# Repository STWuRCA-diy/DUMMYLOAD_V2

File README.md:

IMPORTANT!

Unfortunately, I did not have enough time to verify whether the shared version of the board contains any errors. This is a hobby project and I also had to focus on my day job.

I hope someone from the community will be able to review the design, confirm that everything is correct, or fix any mistakes I may have left behind.

The first version of the board did not include many of the components that are present in the shared version. However, all of them were tested using bodge wiring and then added to the shared design.

Good luck!

DUMMYLOAD_V2

High-Voltage Electronic Dummy Load (Non-Commercial, Open-Source)

DUMMYLOAD_V2 is an open-source, non-commercial electronic dummy load designed for testing high-voltage linear power supplies, especially those used in tube (valve) amplifier circuits.

The project includes hardware (PCB), firmware, and mechanical enclosure, forming a complete DIY measurement and load solution for HV power supply development and testing.

Key Features
	•	Adjustable constant-current load
	•	High-voltage measurement via resistor divider
	•	Current measurement using INA219
	•	Protection logic implemented in firmware
	•	Stand-alone operation (no PC required)

Electrical Characteristics
	•	Load mode: Constant Current (CC)
	•	Current regulation range: 0 – ~400 mA (firmware-controlled, step-based)
	•	Voltage measurement

⚠️ HIGH VOLTAGE WARNING

This project is intended for experienced users.

High voltages used in tube power supplies can be lethal.

	•	Use proper insulation and creepage distances
	•	Never touch the circuit during operation
	•	The author assumes no responsibility for misuse

If you are not comfortable working with HV — do not build or use this device.

⸻

📜 License (Very Important)

🔒 Non-Commercial Only

This entire project is licensed under:

Creative Commons Attribution-NonCommercial 4.0 International
(CC BY-NC 4.0)

🍺 Friendly Note

If you ever meet me in person and find this project useful,
you owe me a beer.

If we happen to be in a country where it is legal,
a joint is also acceptable 🙂

This is a friendly gesture — not a legal obligation.

⸻

❤️ Credits

Designed and shared by STWuRCA-diy
DIY spirit, tube amps & open hardware 🤘

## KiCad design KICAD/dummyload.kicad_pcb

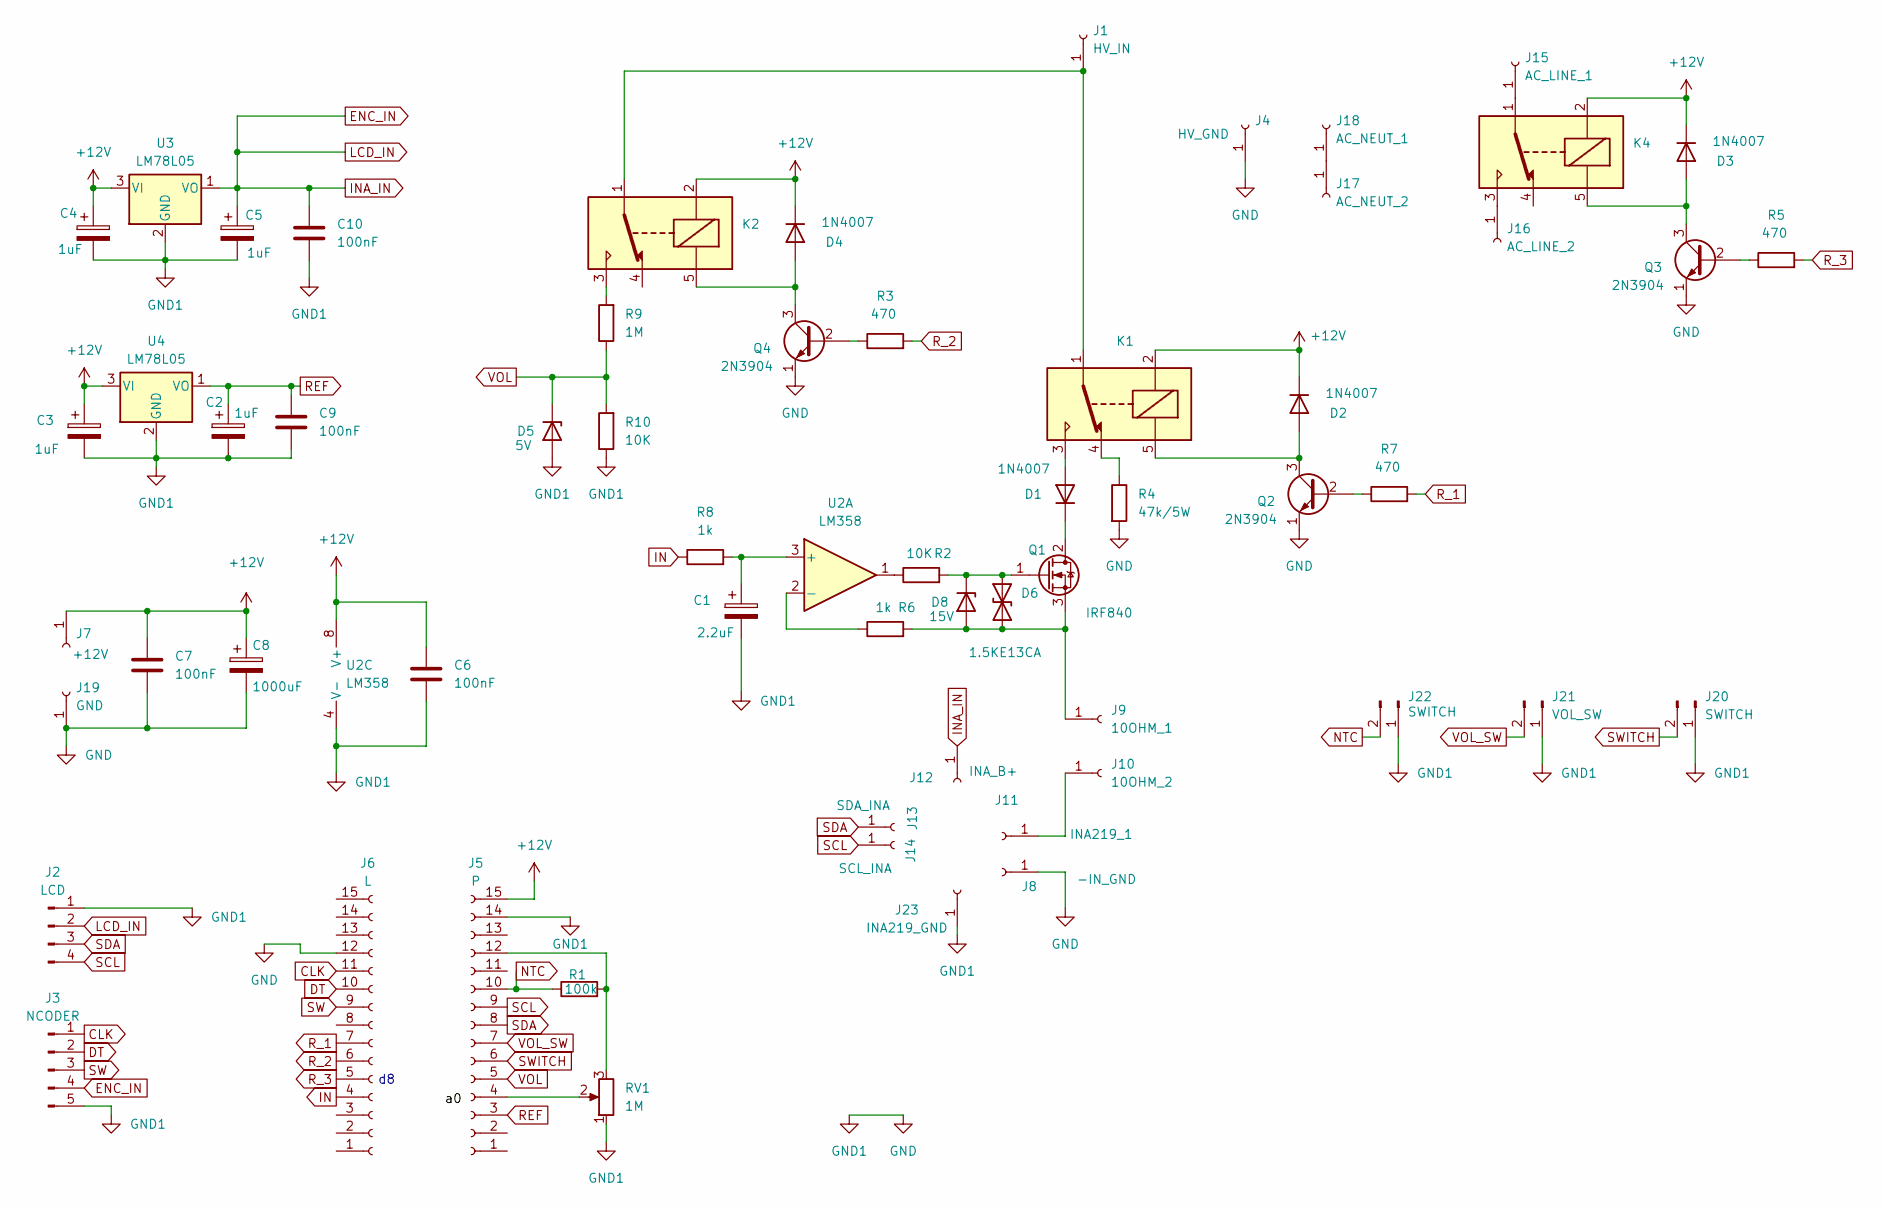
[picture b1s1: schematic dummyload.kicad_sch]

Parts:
C1: 2.2uF; CP_Radial_D4.0mm_P2.00mm
C2, C3, C4, C5: 1uF; CP_Radial_D4.0mm_P2.00mm
C6, C7, C9, C10: 100nF; C_Disc_D3.0mm_W2.0mm_P2.50mm
C8: 1000uF; CP_Radial_D8.0mm_P5.00mm
D1, D2, D3, D4: 1N4007; D_DO-41_SOD81_P10.16mm_Horizontal
D5: 5V; D_A-405_P7.62mm_Horizontal
D6: 1.5KE13CA; D_DO-41_SOD81_P10.16mm_Horizontal
D8: 15V; D_A-405_P10.16mm_Horizontal
J1: HV_IN; SolderWire-0.5sqmm_1x01_D0.9mm_OD2.1mm
J2: LCD; PinHeader_1x04_P2.54mm_Vertical
J3: NCODER; PinHeader_1x05_P2.54mm_Vertical
J4: HV_GND; SolderWire-0.5sqmm_1x01_D0.9mm_OD2.1mm
J5: P; PinHeader_1x15_P2.54mm_Vertical
J6: L; PinHeader_1x15_P2.54mm_Vertical
J7: +12V; SolderWire-0.5sqmm_1x01_D0.9mm_OD2.1mm
J8: -IN_GND; SolderWire-0.5sqmm_1x01_D0.9mm_OD2.1mm
J9: 10OHM_1; SolderWire-0.5sqmm_1x01_D0.9mm_OD2.1mm
J10: 10OHM_2; SolderWire-0.5sqmm_1x01_D0.9mm_OD2.1mm
J11: INA219_1; SolderWire-0.5sqmm_1x01_D0.9mm_OD2.1mm
J12: INA_B+; SolderWire-0.5sqmm_1x01_D0.9mm_OD2.1mm
J13: SDA_INA; SolderWire-0.5sqmm_1x01_D0.9mm_OD2.1mm
J14: SCL_INA; SolderWire-0.5sqmm_1x01_D0.9mm_OD2.1mm
J15: AC_LINE_1; SolderWire-0.5sqmm_1x01_D0.9mm_OD2.1mm
J16: AC_LINE_2; SolderWire-0.5sqmm_1x01_D0.9mm_OD2.1mm
J17: AC_NEUT_2; SolderWire-0.5sqmm_1x01_D0.9mm_OD2.1mm
J18: AC_NEUT_1; SolderWire-0.5sqmm_1x01_D0.9mm_OD2.1mm
J19: GND; SolderWire-0.5sqmm_1x01_D0.9mm_OD2.1mm
J20, J22: SWITCH; PinHeader_1x02_P2.54mm_Vertical
J21: VOL_SW; PinHeader_1x02_P2.54mm_Vertical
J23: INA219_GND; SolderWire-0.5sqmm_1x01_D0.9mm_OD2.1mm
K1, K2, K4: SANYOU_SRD_Form_C; Relay_SPDT_SANYOU_SRD_Series_Form_C
Q1: IRF840; TO-220-3_Vertical
Q2, Q3, Q4: 2N3904; TO-92_Inline
R1: 100k; R_Axial_DIN0207_L6.3mm_D2.5mm_P10.16mm_Horizontal
R2, R10: 10K; R_Axial_DIN0207_L6.3mm_D2.5mm_P10.16mm_Horizontal
R3, R5, R7: 470; R_Axial_DIN0207_L6.3mm_D2.5mm_P10.16mm_Horizontal
R4: 47k/5W; R_Axial_DIN0309_L9.0mm_D3.2mm_P12.70mm_Horizontal
R6, R8: 1k; R_Axial_DIN0207_L6.3mm_D2.5mm_P10.16mm_Horizontal
R9: 1M; R_Axial_DIN0207_L6.3mm_D2.5mm_P10.16mm_Horizontal
RV1: 1M; Potentiometer_Vishay_T73YP_Vertical
U2: LM358; CERDIP-8_W7.62mm_SideBrazed
U3, U4: LM78L05; TO-92_Inline

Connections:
+12V: C3.1, C4.1, C6.1, C7.1, C8.1, D2.1 (K), D3.1 (K), D4.1 (K), J5.15, J7.1, K1.2, K2.2, K4.2, U2.8 (V+), U3.3 (VI), U4.3 (VI)
CLK: J3.1, J6.11
DT: J3.2, J6.10
ENC_IN: C5.1, C10.1, J2.2, J3.4, J12.1, U3.1 (VO)
GND: C1.2, C2.2, C3.2, C4.2, C5.2, C6.2, C7.2, C8.2, C9.2, C10.2, D5.2 (A), J2.1, J3.5, J4.1, J5.14, J6.12, J8.1, J19.1, J20.1, J21.1, J22.1, J23.1, Q2.1 (E), Q3.1 (E), Q4.1 (E), R4.2, R10.1, RV1.1, U2.4 (V-), U3.2 (GND), U4.2 (GND)
IN: J6.4, R8.1
NTC: J5.10, J22.2, R1.1
unnamed: D1.2 (A), K1.3
unnamed: D1.1 (K), Q1.2 (D)
unnamed: D2.2 (A), K1.5, Q2.3 (C)
unnamed: D3.2 (A), K4.5, Q3.3 (C)
unnamed: D4.2 (A), K2.5, Q4.3 (C)
unnamed: D6.1 (A1), D8.1 (K), Q1.1 (G), R2.2
unnamed: D6.2 (A2), D8.2 (A), J9.1, Q1.3 (S), R6.2
unnamed: J1.1, K1.1, K2.1
unnamed: J5.4, RV1.2
unnamed: J5.12, R1.2, RV1.3
unnamed: J10.1, J11.1
unnamed: J15.1, K4.1
unnamed: J16.1, K4.3
unnamed: J17.1, J18.1
unnamed: K1.4, R4.1
unnamed: K2.3, R9.2
unnamed: Q2.2 (B), R7.1
unnamed: Q3.2 (B), R5.1
unnamed: Q4.2 (B), R3.1
unnamed: R2.1, U2.1
unnamed: C1.1, R8.2, U2.3 (+)
unnamed: R6.1, U2.2 (-)
REF: C2.1, C9.1, J5.3, U4.1 (VO)
R_1: J6.7, R7.2
R_2: J6.6, R3.2
R_3: J6.5, R5.2
SCL: J2.4, J5.9, J14.1
SDA: J2.3, J5.8, J13.1
SW: J3.3, J6.9
SWITCH: J5.6, J20.2
VOL: D5.1 (K), J5.5, R9.1, R10.2
VOL_SW: J5.7, J21.2

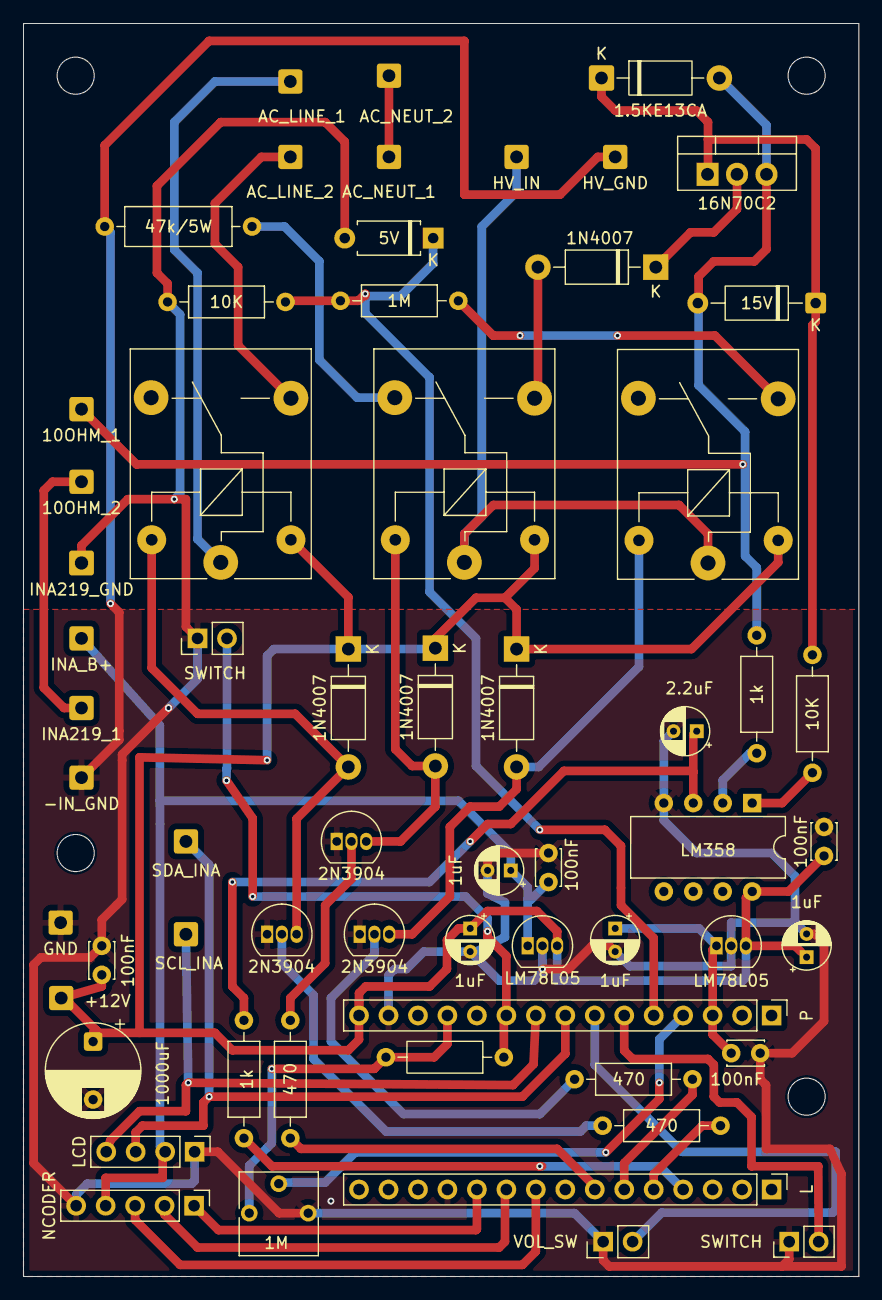
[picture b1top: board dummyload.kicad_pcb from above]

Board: 2 copper layers, 72.0 x 108.0 mm, 61 parts (0 on the bottom side), 39 nets.

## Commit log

2025-12-25 Add CC BY-NC 4.0 license
